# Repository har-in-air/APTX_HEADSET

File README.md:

# APTX_HEADSET

Kicad [schematic](aptx_headset.pdf) and PCB layout for an APTX bluetooth audio headset.
* FT-3188 Qualcomm CSR8645 module 
* OPA1664 opamps for differential to single-ended audio conversion, and headphone buffer.
* LM358 buffered virtual ground for single-ended opamp power supply.
* Two layers, 65 mm x 32 mm.

## Top

## Bottom

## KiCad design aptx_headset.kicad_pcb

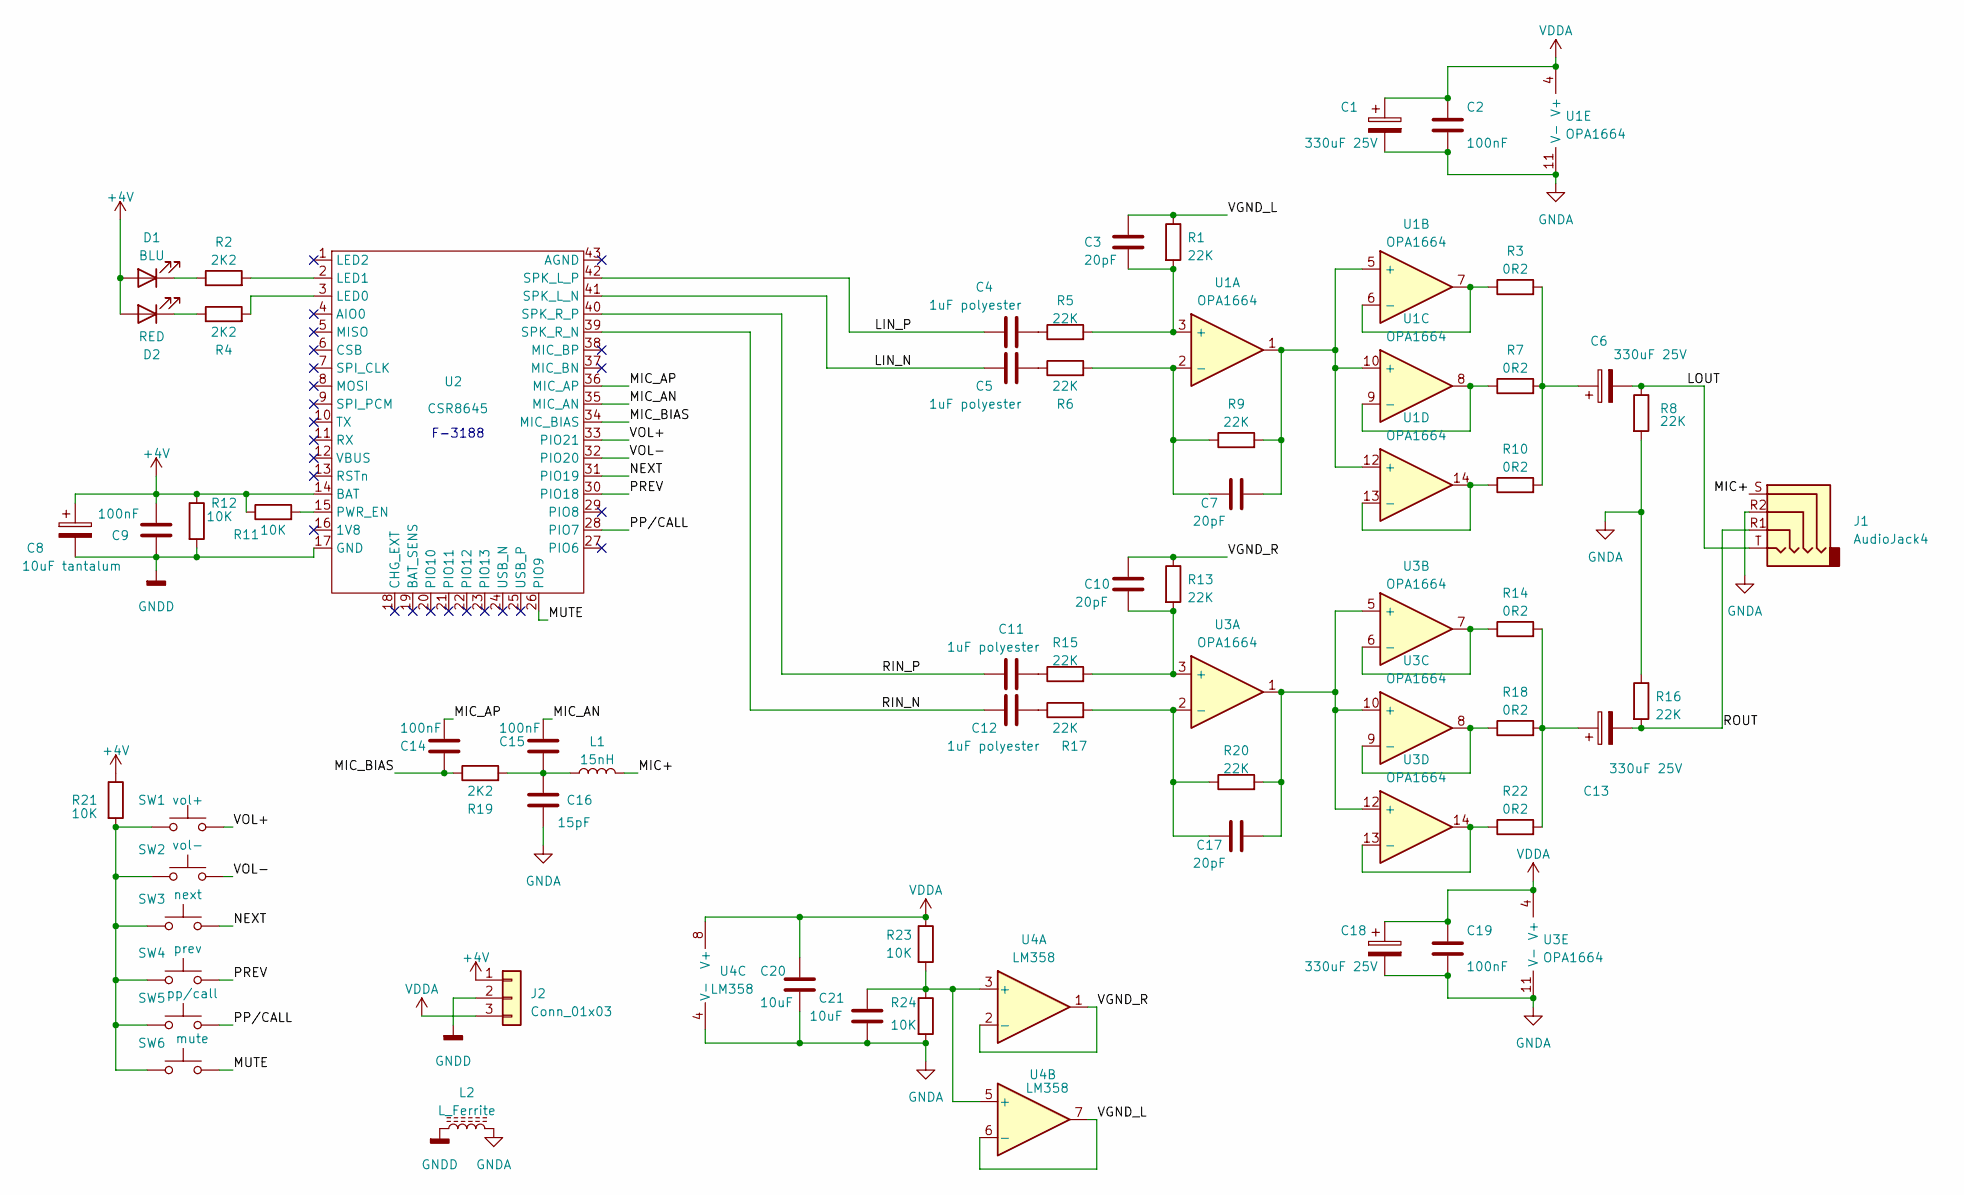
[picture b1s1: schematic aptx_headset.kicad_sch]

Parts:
C1, C6, C13, C18: 330uF 25V; CP_Elec_8x10
C2, C9, C14, C15, C19: 100nF; C_0603_1608Metric_Pad1.08x0.95mm_HandSolder
C3, C7, C10, C17: 20pF; C_0603_1608Metric_Pad1.08x0.95mm_HandSolder
C4, C5, C11, C12: 1uF polyester; C_Rect_L7.0mm_W6.0mm_P5.00mm
C8: 10uF tantalum; C_1206_3216Metric_Pad1.33x1.80mm_HandSolder
C16: 15pF; C_0603_1608Metric_Pad1.08x0.95mm_HandSolder
C20, C21: 10uF; C_0603_1608Metric_Pad1.08x0.95mm_HandSolder
D1: BLU; LED_0603_1608Metric_Pad1.05x0.95mm_HandSolder
D2: RED; LED_0603_1608Metric_Pad1.05x0.95mm_HandSolder
J1: AudioJack4; Jack_3.5mm_PJ320D_Horizontal
J2: Conn_01x03; PinHeader_1x03_P2.54mm_Vertical
L1: 15nH; L_0805_2012Metric_Pad1.15x1.40mm_HandSolder
L2: L_Ferrite; C_0603_1608Metric_Pad1.08x0.95mm_HandSolder
R1, R5, R6, R8, R9, R13, R15, R16, R17, R20: 22K; R_0603_1608Metric_Pad0.98x0.95mm_HandSolder
R2, R4, R19: 2K2; R_0603_1608Metric_Pad0.98x0.95mm_HandSolder
R3, R7, R10, R14, R18, R22: 0R2; R_2512_6332Metric_Pad1.40x3.35mm_HandSolder
R11, R12, R21, R23, R24: 10K; R_0603_1608Metric_Pad0.98x0.95mm_HandSolder
SW1: vol+; SW_Push_SPST_NO_Alps_SKRK
SW2: vol-; SW_Push_SPST_NO_Alps_SKRK
SW3: next; SW_Push_SPST_NO_Alps_SKRK
SW4: prev; SW_Push_SPST_NO_Alps_SKRK
SW5: pp/call; SW_Push_SPST_NO_Alps_SKRK
SW6: mute; SW_Push_SPST_NO_Alps_SKRK
U1, U3: OPA1664; SOIC-14_3.9x8.7mm_P1.27mm
U2: CSR8645; csr8645_f3188
U4: LM358; SOIC-8_3.9x4.9mm_P1.27mm

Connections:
+4V: C8.1, C9.2, D1.2 (A), D2.2 (A), J2.1, R11.1, R12.1, R21.1, U2.14 (BAT)
/LIN_N: C5.1, U2.41 (SPK_L_N)
/LIN_P: C4.1, U2.42 (SPK_L_P)
/LOUT: C6.2, J1.T, R8.1
/MIC+: J1.S, L1.2
/MIC_AN: C15.1, U2.35 (MIC_AN)
/MIC_AP: C14.1, U2.36 (MIC_AP)
/MIC_BIAS: C14.2, R19.1, U2.34 (MIC_BIAS)
/MUTE: SW6.2, U2.26 (PIO9)
/NEXT: SW3.2, U2.31 (PIO19)
/PP/CALL: SW5.2, U2.28 (PIO7)
/PREV: SW4.2, U2.30 (PIO18)
/RIN_N: C12.1, U2.39 (SPK_R_N)
/RIN_P: C11.1, U2.40 (SPK_R_P)
/ROUT: C13.2, J1.R1, R16.2
/VGND_L: C3.1, R1.1, U4.6 (-), U4.7
/VGND_R: C10.1, R13.1, U4.1, U4.2 (-)
/VOL+: SW1.2, U2.33 (PIO21)
/VOL-: SW2.2, U2.32 (PIO20)
GNDA: C1.2, C2.2, C16.2, C18.2, C19.2, C20.2, C21.2, J1.R2, L2.2, R8.2, R16.1, R24.2, U1.11 (V-), U3.11 (V-), U4.4 (V-)
GNDD: C8.2, C9.1, J2.2, L2.1, R12.2, U2.17 (GND)
unnamed: C4.2, R5.1
unnamed: C5.2, R6.1
unnamed: C6.1, R3.2, R7.2, R10.2
unnamed: C11.2, R15.1
unnamed: C12.2, R17.1
unnamed: C13.1, R14.2, R18.2, R22.2
unnamed: C15.2, C16.1, L1.1, R19.2
unnamed: D1.1 (K), R2.1
unnamed: D2.1 (K), R4.1
unnamed: R21.2, SW1.1, SW2.1, SW3.1, SW4.1, SW5.1, SW6.1
unnamed: C3.2, R1.2, R5.2, U1.3 (+)
unnamed: C7.1, R6.2, R9.1, U1.2 (-)
unnamed: C7.2, R9.2, U1.1, U1.5 (+), U1.10 (+), U1.12 (+)
unnamed: R3.1, U1.6 (-), U1.7
unnamed: R7.1, U1.8, U1.9 (-)
unnamed: R10.1, U1.13 (-), U1.14
unnamed: R4.2, U2.3 (LED0)
unnamed: R2.2, U2.2 (LED1)
unnamed: R11.2, U2.15 (PWR_EN)
unnamed: C10.2, R13.2, R15.2, U3.3 (+)
unnamed: C17.1, R17.2, R20.1, U3.2 (-)
unnamed: C17.2, R20.2, U3.1, U3.5 (+), U3.10 (+), U3.12 (+)
unnamed: R14.1, U3.6 (-), U3.7
unnamed: R18.1, U3.8, U3.9 (-)
unnamed: R22.1, U3.13 (-), U3.14
unnamed: C21.1, R23.2, R24.1, U4.3 (+), U4.5 (+)
VDDA: C1.1, C2.1, C18.1, C19.1, C20.1, J2.3, R23.1, U1.4 (V+), U3.4 (V+), U4.8 (V+)

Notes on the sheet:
F-3188

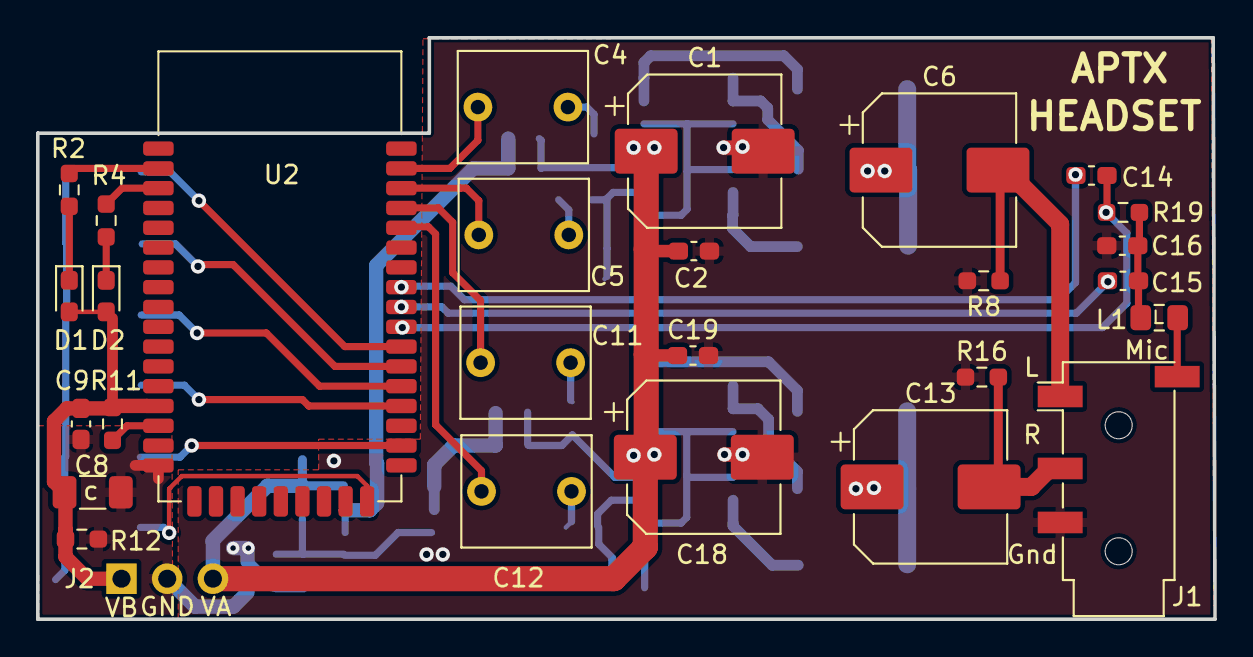
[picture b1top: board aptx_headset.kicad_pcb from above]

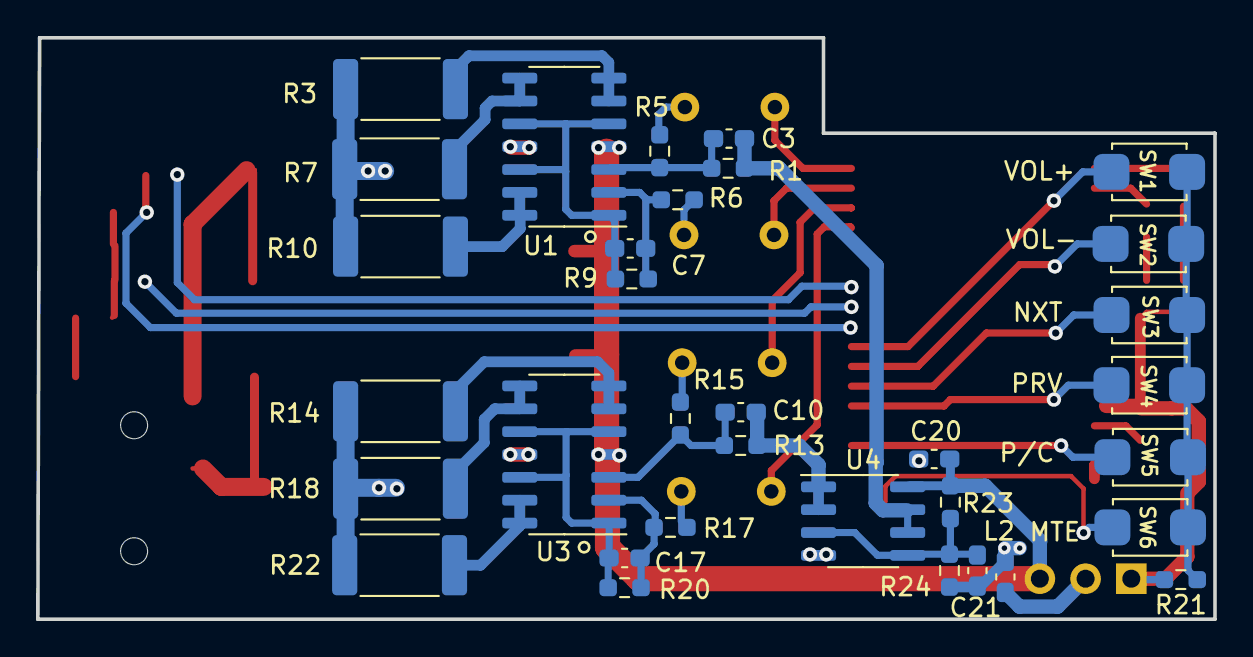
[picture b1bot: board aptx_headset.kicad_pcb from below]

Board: 2 copper layers, 65.4 x 32.3 mm, 61 parts (33 on the bottom side), 48 nets.

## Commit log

2022-04-21 add readme
2022-04-21 add 3d pics
2022-04-22 separate buffered VGND
2022-04-23 move buttons
2022-04-23 move silkscreen
